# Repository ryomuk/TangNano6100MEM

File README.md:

# TangNano6100MEM
Memory systems and peripherals implemented on Tang Nano 20K for Intersil IM6100 PDP-8 Processor

This document is written mostly in Japanese, so please use machine translation if necessary.

# 概要
- PDP-8の命令セットを持つCPU「Intersil IM6100」のメモリシステムと周辺回路をFPGA(TangNano20K)上に実装する試みです．
- FPGAに実装するのはメモリ，UART, HDDなどの周辺装置の部分だけで，CPU自体は本物を使用します．ソフトウェアやFPGAによるシミュレータやエミュレータではなく，実物のCPUを動かします．
- "TangNano6100"だとTangNano上にIM6100を実装したみたいな名前になってしまうので，"MEM"を付けて"TangNano6100MEM"という名前になっています．
- モニタプログラムとして，Haruo Asano氏による[Universal Monitor](https://electrelic.com/electrelic/node/1317)IM6100版をControl Panel空間で動くように改変したものを搭載しました．MITライセンスだったので，使用した部分のソースを同梱しています．

## 最近の主な話題
- 2026/01/28: 初版公開
- 2026/02/01: version 20260201, 紙テープエミュレータ実装
- 2026/02/02: version 20260202, 割り込み関連のバグ修正
- 2026/02/02: CP空間のuniversal monitorにコンテキストの保存復帰を実装しました．
- 2026/02/06: version 20260206, 拡張メモリ関連の微修正
- 2026/02/06: OS/8のRK2, RK3を有効化する方法についてのドキュメントを追加．
  
## 主なファイル一覧
```
.
├── doc                      : 説明用文書
├── hdl                      : Gowin EDA用プロジェクト
│   ├── old                 : 旧版のバックアップ(あれば)
│   └── TangNano6100MEM_project: HDLソース一式
│       └── src
│            ├── dbglog.v   : debug log用モジュール
│            ├── mem.v      : メモリ初期データ(OS/8 bootloader)
│            ├── mem_cp.v   : CPメモリデータ(unimon)
│            ├── sdhd.v     : HDエミュレータモジュール
│            ├── sdtape.v   : 紙tapeエミュレータモジュール
│            ├── switch.v   : スイッチ用モジュール
│            ├── TangNano6100MEM_project.sdc : 時間制約(適当)
│            ├── tn20k.cst  :  物理制約(ピンアサイン)
│            ├── top.v      : メインプログラム
│            ├── uart.v     : uartモジュール
│            ├── ws2812.v   : WS2812モジュール
│            └── ws2812_matrix.v : WS2812 matrix用モジュール
├── images                   : 文書用画像ファイル
├── LICENSE
├── pcb
│   └── rev2.1 :  回路図，基板データ等(KiCAD 9用)
├── README.md   : このファイル
└── tools
    ├── papertape
    │   └── ptp2v.c    : 紙テープバイナリ変換用ソフト
    ├── sample          : bootやテスト用プログラム(unimonで書く用)
    └── unimon          : Universal Monitor
        ├── im6100      : IM6100 Control Panel版
        └── LICENSE.txt : 上記のライセンスファイル

```

各種説明は[doc/](./doc/)に項目に分けて記載しています．
- [更新履歴](doc/01_updatelog.md)
- [基板関連](doc/02_PCB.md)
- [FPGA関連](doc/03_FPGA.md)
- [インターフェース](doc/04_Interface.md)
- [SDメモリ](doc/05_SDmemory.md)
- [応用例](doc/06-0_applications.md)
  - [ベアメタル](doc/06-1_baremetal.md)
  - [紙テープソフト](doc/06-2_papertape.md)
  - [OS/8](doc/06-3_os8.md)
    - [RK2-3diskの有効化](doc/06-3_os8_reconfig.md)
- [デバッグツール](doc/07_debugtool.md)
- [関連情報・参考資料](doc/08_references.md)

## その他
以下，雑多な情報です．

### 動作状況
- 紙テープソフトやOS/8およびOS/8上で動く言語処理系などがある程度動作します．
- OS/8のBASICで簡単なプログラムを入力したりセーブ/ロードしたりできます．
  - STRTRK.BAやSNOOPY.BAが動きました．
- コントロールパネル空間でUniversal Monitorが動きます．

### 既知の問題
- ステップ実行後に戻ってくるとおかしくなることがある．
- ~~OS/8版のFOCALが動かない．おそらく割り込み関連の問題．~~ → やはり割り込みの問題でした．20260202版で修正して解決．
- ~~OS/8でDIR SYS: はできるが DIR RKA0: は止まる．~~ → PDP/8ハンドブックの誤植が原因でした．RK_DONEフラグを修正したら動くようになりました．
- ~~OS/8 BASICでSTRTRK.BAやSNOOPY.BAが動かない．~~ 動きました．

### 今後の予定，ToDo
- 紙テープイメージからOS/8のディスクイメージを作成．
  - → ある程度はできたのですが，CCL.SVがうまく作れなかったりEPICの動作が不安定なのであきらめました．
- 磁気テープドライブエミュレータ実装．(紙テープは実装済なので，必要でなければやらないかも)
  - → いろいろ面倒な仕様があったのであきらめました．

<!--
# 動画
- 未
-->

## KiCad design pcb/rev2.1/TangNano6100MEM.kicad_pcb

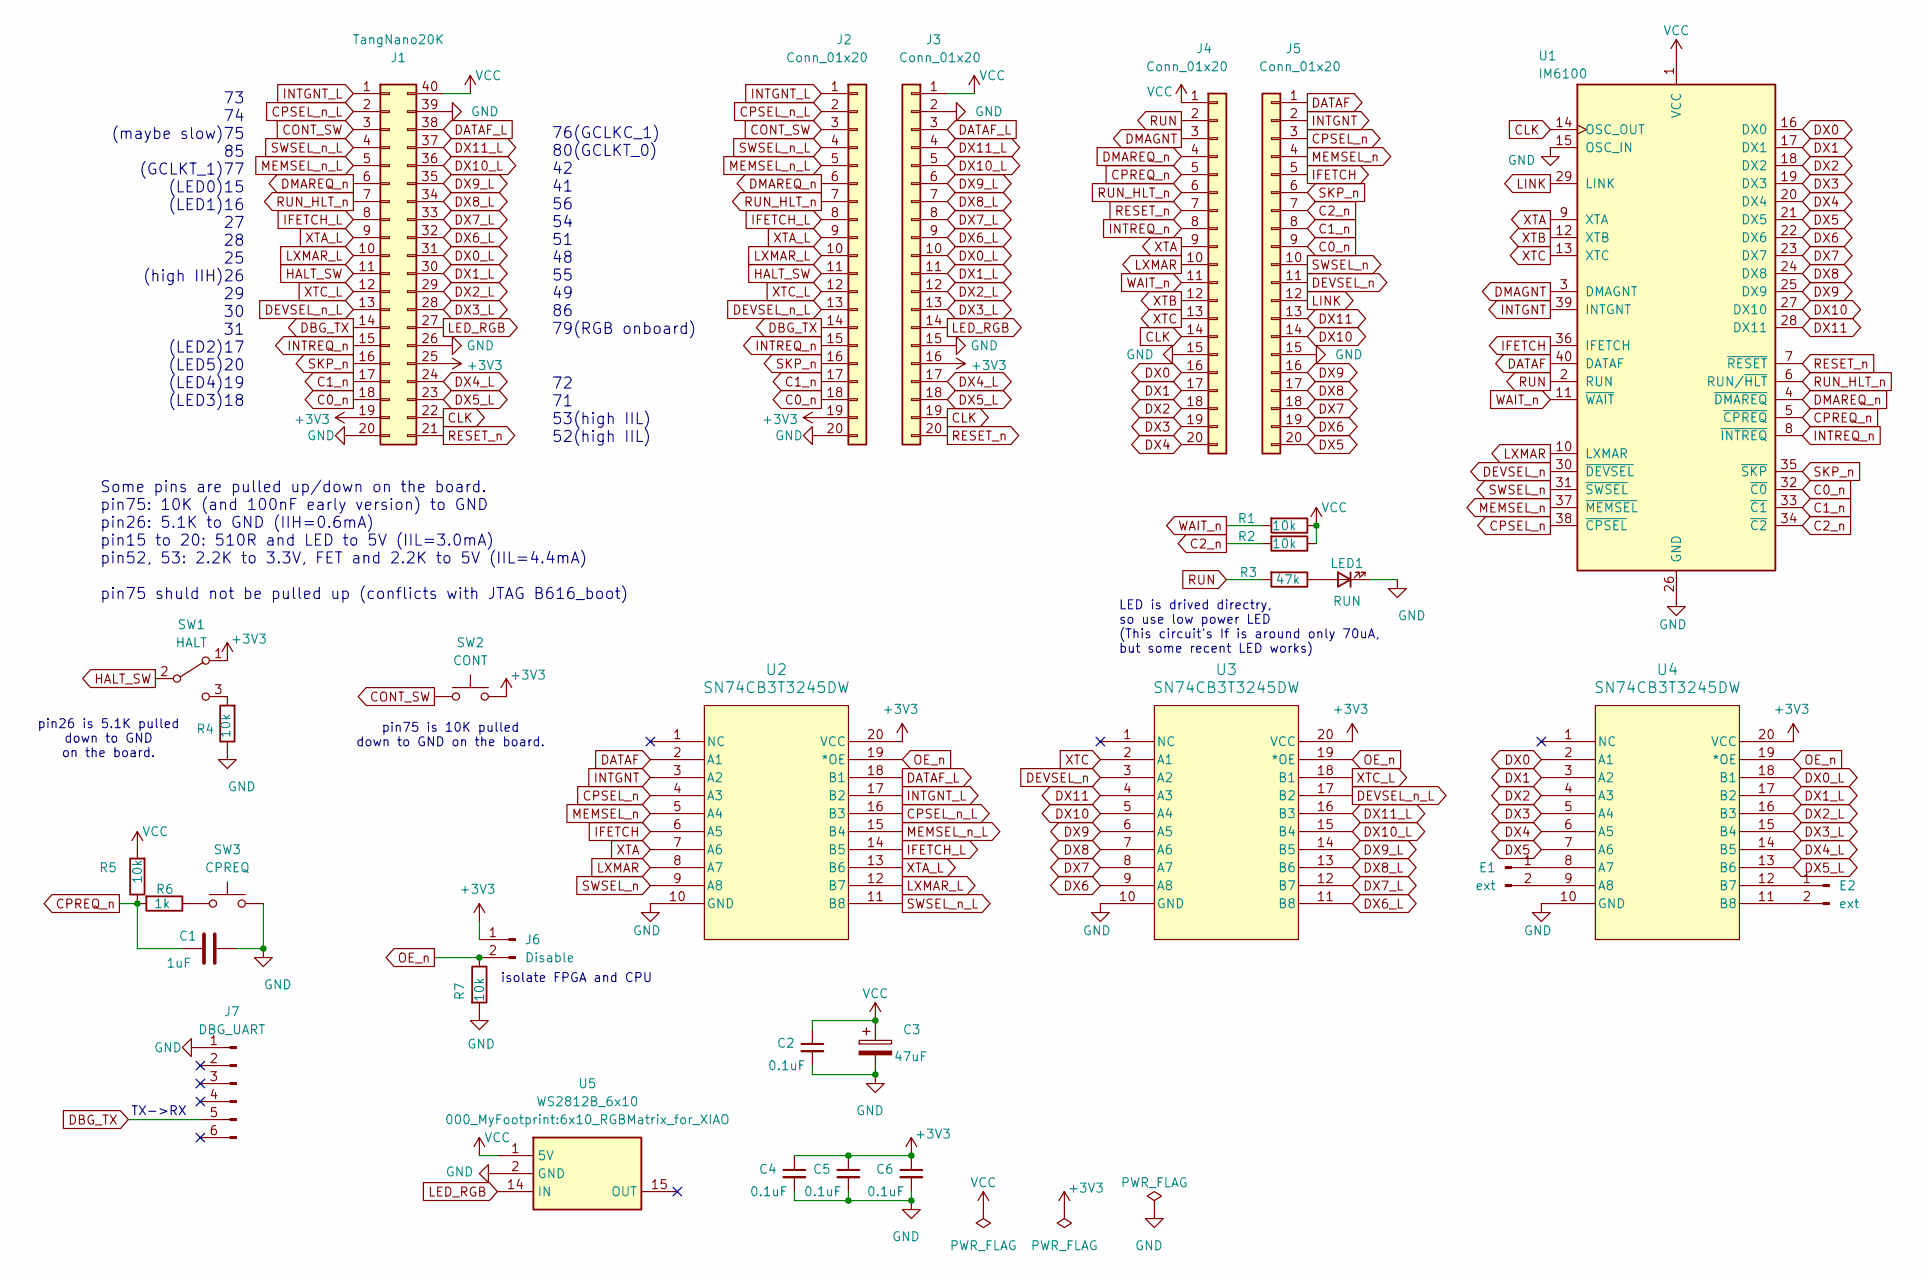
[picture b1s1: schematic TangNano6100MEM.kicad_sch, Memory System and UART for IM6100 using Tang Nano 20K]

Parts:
C1: 1uF; C_Disc_D4.3mm_W1.9mm_P5.00mm
C2, C4, C5, C6: 0.1uF; C_Disc_D5.0mm_W2.5mm_P2.50mm
C3: 47uF; CP_Radial_D6.3mm_P2.50mm
E1, E2: ext; TH_1x02_P1.27mm
J1: TangNano20K; DIP-40_W20.32mm800mil_Socket
J2, J3, J4, J5: Conn_01x20; PinSocket_1x20_P2.54mm_Vertical
J6: Disable; PinHeader_1x02_P2.54mm_Vertical
J7: DBG_UART; PinHeader_1x06_P2.54mm_Horizontal
LED1: RUN; LED_D3.0mm
R1, R2, R4, R5, R7: 10k; R_Axial_DIN0207_L6.3mm_D2.5mm_P7.62mm_Horizontal
R3: 47k; R_Axial_DIN0207_L6.3mm_D2.5mm_P7.62mm_Horizontal
R6: 1k; R_Axial_DIN0207_L6.3mm_D2.5mm_P7.62mm_Horizontal
SW1: HALT; SW_SPDT_Toggle
SW2: CONT; SW_PUSH_6mm_H4.3mm
SW3: CPREQ; SW_PUSH_6mm_H4.3mm
U1: IM6100; DIP-40_W15.24mm_Socket
U2, U3, U4: SN74CB3T3245DW; DW20
U5: WS2812B_6x10; 6x10_RGBMatrix_for_XIAO

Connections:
+3V3: C4.1, C5.1, C6.1, J1.19, J1.25, J2.19, J3.16, J6.1, SW1.1 (A), SW2.1, U2.20 (VCC), U3.20 (VCC), U4.20 (VCC)
C0_n: J1.18, J2.18, J5.9, U1.32 (~C0)
C1_n: J1.17, J2.17, J5.8, U1.33 (~C1)
C2_n: J5.7, R2.2, U1.34 (~C2)
CLK: J1.22, J3.19, J4.14, U1.14 (OSC_OUT)
CONT_SW: J1.3, J2.3, SW2.2
CPREQ_n: C1.1, J4.5, R5.1, R6.2, U1.5 (~CPREQ)
CPSEL_n: J5.3, U1.38 (~CPSEL), U2.4 (A3)
CPSEL_n_L: J1.2, J2.2, U2.16 (B3)
DATAF: J5.1, U1.40 (DATAF), U2.2 (A1)
DATAF_L: J1.38, J3.3, U2.18 (B1)
DBG_TX: J1.14, J2.14, J7.5
DEVSEL_n: J5.11, U1.30 (~DEVSEL), U3.3 (A2)
DEVSEL_n_L: J1.13, J2.13, U3.17 (B2)
DMAGNT: J4.3, U1.3 (DMAGNT)
DMAREQ_n: J1.6, J2.6, J4.4, U1.4 (~DMAREQ)
DX0: J4.16, U1.16 (DX0), U4.2 (A1)
DX0_L: J1.31, J3.10, U4.18 (B1)
DX1: J4.17, U1.17 (DX1), U4.3 (A2)
DX1_L: J1.30, J3.11, U4.17 (B2)
DX2: J4.18, U1.18 (DX2), U4.4 (A3)
DX2_L: J1.29, J3.12, U4.16 (B3)
DX3: J4.19, U1.19 (DX3), U4.5 (A4)
DX3_L: J1.28, J3.13, U4.15 (B4)
DX4: J4.20, U1.20 (DX4), U4.6 (A5)
DX4_L: J1.24, J3.17, U4.14 (B5)
DX5: J5.20, U1.21 (DX5), U4.7 (A6)
DX5_L: J1.23, J3.18, U4.13 (B6)
DX6: J5.19, U1.22 (DX6), U3.9 (A8)
DX6_L: J1.32, J3.9, U3.11 (B8)
DX7: J5.18, U1.23 (DX7), U3.8 (A7)
DX7_L: J1.33, J3.8, U3.12 (B7)
DX8: J5.17, U1.24 (DX8), U3.7 (A6)
DX8_L: J1.34, J3.7, U3.13 (B6)
DX9: J5.16, U1.25 (DX9), U3.6 (A5)
DX9_L: J1.35, J3.6, U3.14 (B5)
DX10: J5.14, U1.27 (DX10), U3.5 (A4)
DX10_L: J1.36, J3.5, U3.15 (B4)
DX11: J5.13, U1.28 (DX11), U3.4 (A3)
DX11_L: J1.37, J3.4, U3.16 (B3)
GND: C1.2, C2.2, C3.2, C4.2, C5.2, C6.2, J1.20, J1.26, J1.39, J2.20, J3.2, J3.15, J4.15, J5.15, J7.1, LED1.1 (K), R4.1, R7.2, SW3.1, U1.15 (OSC_IN), U1.26 (GND), U2.10 (GND), U3.10 (GND), U4.10 (GND), U5.2 (GND)
HALT_SW: J1.11, J2.11, SW1.2 (B)
IFETCH: J5.5, U1.36 (IFETCH), U2.6 (A5)
IFETCH_L: J1.8, J2.8, U2.14 (B5)
INTGNT: J5.2, U1.39 (INTGNT), U2.3 (A2)
INTGNT_L: J1.1, J2.1, U2.17 (B2)
INTREQ_n: J1.15, J2.15, J4.8, U1.8 (~INTREQ)
LED_RGB: J1.27, J3.14, U5.14 (IN)
LINK: J5.12, U1.29 (LINK)
LXMAR: J4.10, U1.10 (LXMAR), U2.8 (A7)
LXMAR_L: J1.10, J2.10, U2.12 (B7)
MEMSEL_n: J5.4, U1.37 (~MEMSEL), U2.5 (A4)
MEMSEL_n_L: J1.5, J2.5, U2.15 (B4)
unnamed: E1.1, U4.8 (A7)
unnamed: E1.2, U4.9 (A8)
unnamed: E2.1, U4.12 (B7)
unnamed: E2.2, U4.11 (B8)
unnamed: LED1.2 (A), R3.1
unnamed: R6.1, SW3.2
unnamed: R4.2, SW1.3 (C)
OE_n: J6.2, R7.1, U2.19 (*OE), U3.19 (*OE), U4.19 (*OE)
RESET_n: J1.21, J3.20, J4.7, U1.7 (~RESET)
RUN: J4.2, R3.2, U1.2 (RUN)
RUN_HLT_n: J1.7, J2.7, J4.6, U1.6 (RUN/~HLT)
SKP_n: J1.16, J2.16, J5.6, U1.35 (~SKP)
SWSEL_n: J5.10, U1.31 (~SWSEL), U2.9 (A8)
SWSEL_n_L: J1.4, J2.4, U2.11 (B8)
VCC: C2.1, C3.1, J1.40, J3.1, J4.1, R1.1, R2.1, R5.2, U1.1 (VCC), U5.1 (5V)
WAIT_n: J4.11, R1.2, U1.11 (~WAIT)
XTA: J4.9, U1.9 (XTA), U2.7 (A6)
XTA_L: J1.9, J2.9, U2.13 (B6)
XTB: J4.12, U1.12 (XTB)
XTC: J4.13, U1.13 (XTC), U3.2 (A1)
XTC_L: J1.12, J2.12, U3.18 (B1)

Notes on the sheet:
TX->RX
72 71 53(high IIL) 52(high IIL)
73 74 (maybe slow)75 85 (GCLKT_1)77 (LED0)15 (LED1)16 27 28 25 (high IIH)26 29 30 31 (LED2)17 (LED5)20 (LED4)19 (LED3)18
76(GCLKC_1) 80(GCLKT_0) 42 41 56 54 51 48 55 49 86 79(RGB onboard)
Some pins are pulled up/down on the board. pin75: 10K (and 100nF early version) to GND pin26: 5.1K to GND (IIH=0.6mA) pin15 to 20: 510R and LED to 5V (IIL=3.0mA) pin52, 53: 2.2K to 3.3V, FET and 2.2K to 5V (IIL=4.4mA) pin75 shuld not be pulled up (conflicts with JTAG B616_boot)
isolate FPGA and CPU
pin26 is 5.1K pulled down to GND on the board.
pin75 is 10K pulled down to GND on the board.
LED is drived directry, so use low power LED (This circuit's If is around only 70uA, but some recent LED works)

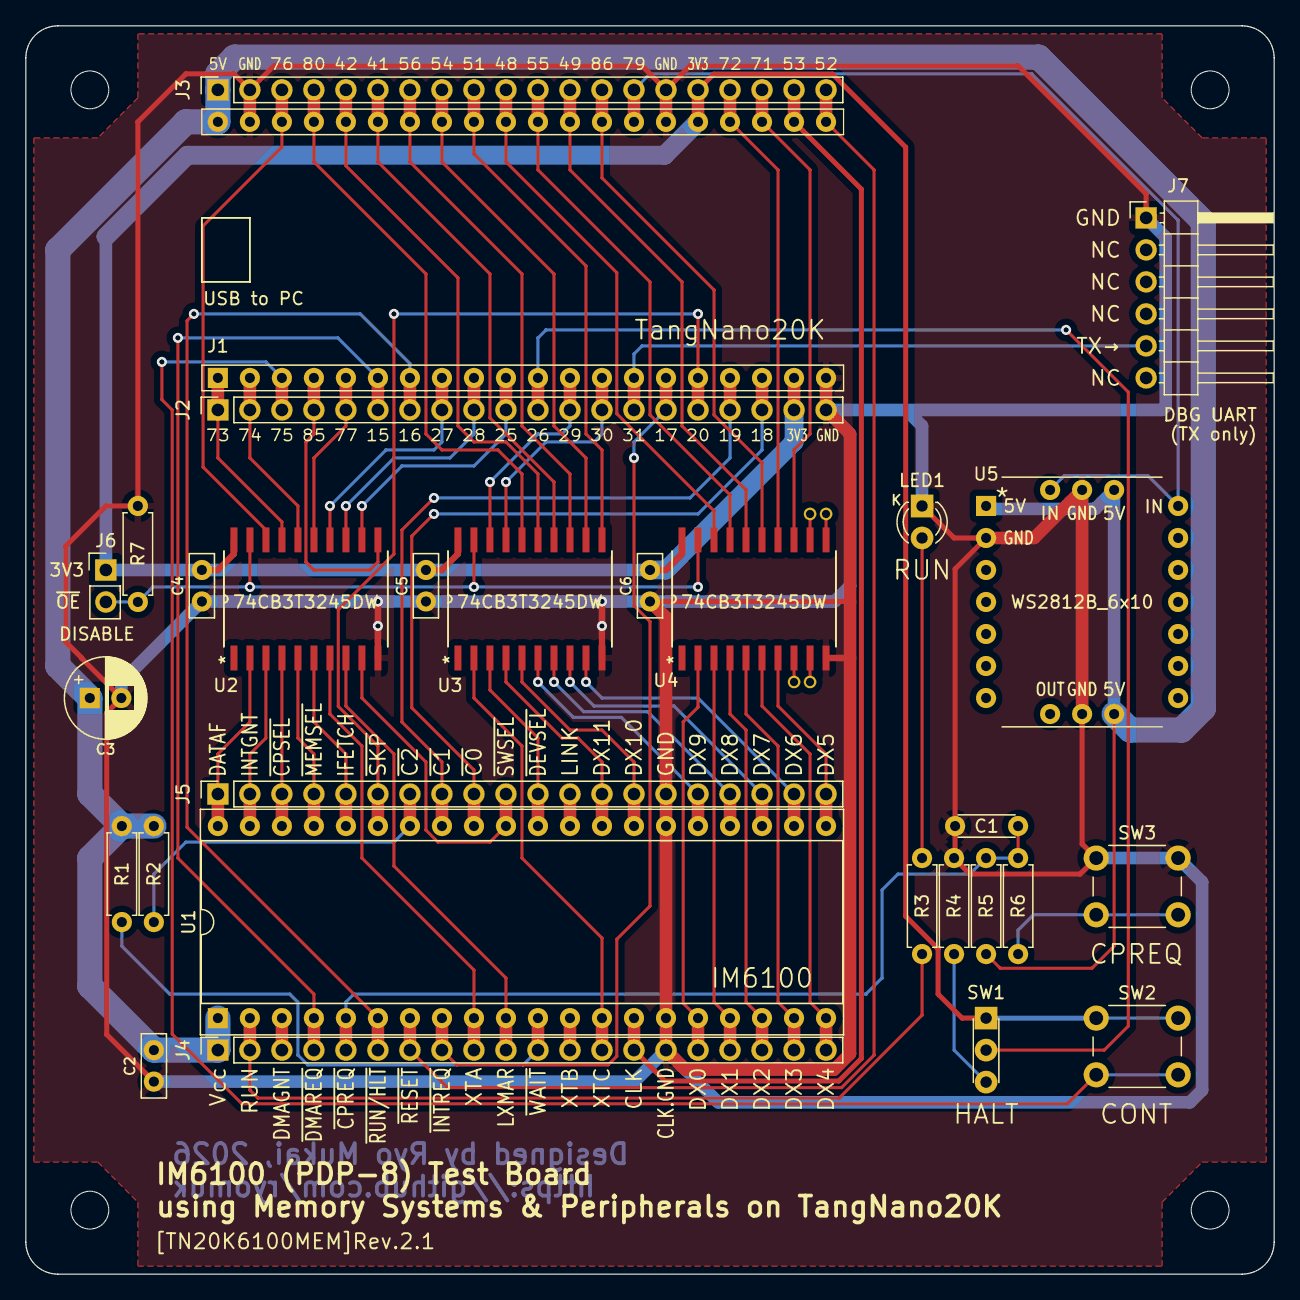
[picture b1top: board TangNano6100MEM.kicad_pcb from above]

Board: 2 copper layers, 99.1 x 99.1 mm, 31 parts (0 on the bottom side), 74 nets.

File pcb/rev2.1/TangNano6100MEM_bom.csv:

Reference,Value,Qty
C1,1uF,1
"C2,C4,C5,C6",0.1uF,4
C3,47uF,1
J1,Conn_01x20 x 2,1
"J2,J3,J4,J5",Conn_01x20,4
J6,01x2,1
J7,01x6,1
LED1,low power LED,1
"R1,R2,R4,R5,R7",10k,5
R3,47k,1
R6,1k,1
SW1,toggle,1
"SW2, SW3",tactile,1
U1,IM6100,1
"U2,U3,U4",SN74CB3T3245DW,3
U5,WS2812B_6x10,1

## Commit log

2026-01-29 hdl updated
2026-01-29 README updated
2026-01-29 doc updated
2026-02-01 20260201 released
2026-02-01 reset REG_SF fixed
2026-02-02 20260202 released
2026-02-02 tools/sample updated
2026-02-02 unimon updated
